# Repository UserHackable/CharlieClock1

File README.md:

## SevenSegmentArrays 

### Board dimensions

* (310000, 200000) original units
* (3.1000, 2.0000) inches
* (78.7400, 50.8000) mm

| Front | Back |
| --- | --- |
|  |  |

## SevenSegmentBreakout 

### Board dimensions

* (365000, 130000) original units
* (3.6500, 1.3000) inches
* (92.7100, 33.0200) mm

| Front | Back |
| --- | --- |
|  |  |

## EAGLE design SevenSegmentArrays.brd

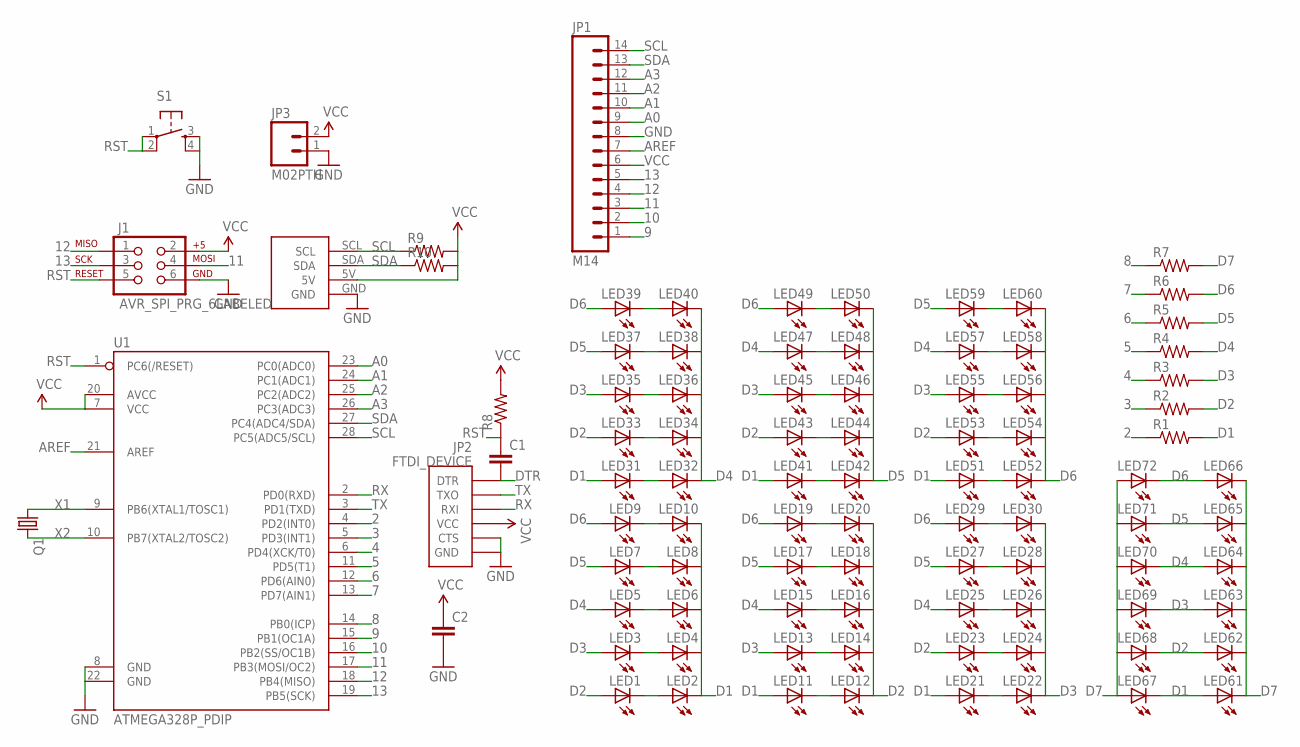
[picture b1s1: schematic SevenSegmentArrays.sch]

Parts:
C1, C2: CAPPTH; CAP-PTH-SMALL
J1: AVR_SPI_PRG_6LABELED; 2X3-NS
JP1: M14; 1X14
JP2: FTDI_DEVICE; FTDI_DEVICE_SIDE
JP3: M02PTH; 1X02
LED1, LED2, LED3, LED4, LED5, LED6, LED7, LED8, LED9, LED10, LED11, LED12, LED13, LED14, LED15, LED16, LED17, LED18, LED19, LED20, LED21, LED22, LED23, LED24, LED25, LED26, LED27, LED28, LED29, LED30, LED31, LED32, LED33, LED34, LED35, LED36, LED37, LED38, LED39, LED40, LED41, LED42, LED43, LED44, LED45, LED46, LED47, LED48, LED49, LED50, LED51, LED52, LED53, LED54, LED55, LED56: LEDRECT; RECTANGLE_LED
LED57, LED58, LED59, LED60, LED61, LED62, LED63, LED64, LED65, LED66, LED67, LED68, LED69, LED70, LED71, LED72: LED3MM
Q1: CRYSTALTC38H; TC38H
R1, R2, R3, R4, R5, R6, R7, R8, R9, R10: RESISTORAXIAL-0.3; AXIAL-0.3
S1: TAC_SWITCHPTH; TACTILE-PTH
U1: ATMEGA328P_PDIP; DIL28-3
U$1: I2C

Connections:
2: R1.P$1 (1), U1.4 (PD2(INT0))
3: R2.P$1 (1), U1.5 (PD3(INT1))
4: R3.P$1 (1), U1.6 (PD4(XCK/T0))
5: R4.P$1 (1), U1.11 (PD5(T1))
6: R5.P$1 (1), U1.12 (PD6(AIN0))
7: R6.P$1 (1), U1.13 (PD7(AIN1))
8: R7.P$1 (1), U1.14 (PB0(ICP))
9: JP1.1, U1.15 (PB1(OC1A))
10: JP1.2, U1.16 (PB2(SS/OC1B))
11: J1.4, JP1.3, U1.17 (PB3(MOSI/OC2))
12: J1.1, JP1.4, U1.18 (PB4(MISO))
13: J1.3, JP1.5, U1.19 (PB5(SCK))
A0: JP1.9, U1.23 (PC0(ADC0))
A1: JP1.10, U1.24 (PC1(ADC1))
A2: JP1.11, U1.25 (PC2(ADC2))
A3: JP1.12, U1.26 (PC3(ADC3))
AREF: JP1.7, U1.21 (AREF)
D1: LED2.C, LED4.C, LED6.C, LED8.C, LED10.C, LED11.A, LED21.A, LED31.A, LED41.A, LED51.A, LED61.A, LED67.K (C), R1.P$2 (2)
D2: LED1.A, LED12.C, LED14.C, LED16.C, LED18.C, LED20.C, LED23.A, LED33.A, LED43.A, LED53.A, LED62.A, LED68.K (C), R2.P$2 (2)
D3: LED3.A, LED13.A, LED22.C, LED24.C, LED26.C, LED28.C, LED30.C, LED35.A, LED45.A, LED55.A, LED63.A, LED69.K (C), R3.P$2 (2)
D4: LED5.A, LED15.A, LED25.A, LED32.C, LED34.C, LED36.C, LED38.C, LED40.C, LED47.A, LED57.A, LED64.A, LED70.K (C), R4.P$2 (2)
D5: LED7.A, LED17.A, LED27.A, LED37.A, LED42.C, LED44.C, LED46.C, LED48.C, LED50.C, LED59.A, LED65.A, LED71.K (C), R5.P$2 (2)
D6: LED9.A, LED19.A, LED29.A, LED39.A, LED49.A, LED52.C, LED54.C, LED56.C, LED58.K (C), LED60.K (C), LED66.A, LED72.K (C), R6.P$2 (2)
D7: LED61.K (C), LED62.K (C), LED63.K (C), LED64.K (C), LED65.K (C), LED66.K (C), LED67.A, LED68.A, LED69.A, LED70.A, LED71.A, LED72.A, R7.P$2 (2)
DTR: C1.2, JP2.P$1 (DTR)
GND: C2.2, J1.6, JP1.8, JP2.P$5 (CTS), JP2.P$6 (GND), JP3.1, S1.3, S1.4, U1.8 (GND), U1.22 (GND), U$1.GND
unnamed: LED1.C, LED2.A
unnamed: LED3.C, LED4.A
unnamed: LED5.C, LED6.A
unnamed: LED7.C, LED8.A
unnamed: LED9.C, LED10.A
unnamed: LED11.C, LED12.A
unnamed: LED13.C, LED14.A
unnamed: LED15.C, LED16.A
unnamed: LED17.C, LED18.A
unnamed: LED19.C, LED20.A
unnamed: LED21.C, LED22.A
unnamed: LED23.C, LED24.A
unnamed: LED25.C, LED26.A
unnamed: LED27.C, LED28.A
unnamed: LED29.C, LED30.A
unnamed: LED31.C, LED32.A
unnamed: LED33.C, LED34.A
unnamed: LED35.C, LED36.A
unnamed: LED37.C, LED38.A
unnamed: LED39.C, LED40.A
unnamed: LED41.C, LED42.A
unnamed: LED43.C, LED44.A
unnamed: LED45.C, LED46.A
unnamed: LED47.C, LED48.A
unnamed: LED49.C, LED50.A
unnamed: LED51.C, LED52.A
unnamed: LED53.C, LED54.A
unnamed: LED55.C, LED56.A
unnamed: LED57.K (C), LED58.A
unnamed: LED59.K (C), LED60.A
RST: C1.1, J1.5, R8.P$1 (1), S1.1, S1.2, U1.1 (PC6(/RESET))
RX: JP2.P$3 (RXI), U1.2 (PD0(RXD))
SCL: JP1.14, R9.P$1 (1), U1.28 (PC5(ADC5/SCL)), U$1.SCL
SDA: JP1.13, R10.P$1 (1), U1.27 (PC4(ADC4/SDA)), U$1.SDA
TX: JP2.P$2 (TXO), U1.3 (PD1(TXD))
VCC: C2.1, J1.2, JP1.6, JP2.P$4 (VCC), JP3.2, R8.P$2 (2), R9.P$2 (2), R10.P$2 (2), U1.7 (VCC), U1.20 (AVCC), U$1.5V
X1: Q1.1, U1.9 (PB6(XTAL1/TOSC1))
X2: Q1.2, U1.10 (PB7(XTAL2/TOSC2))

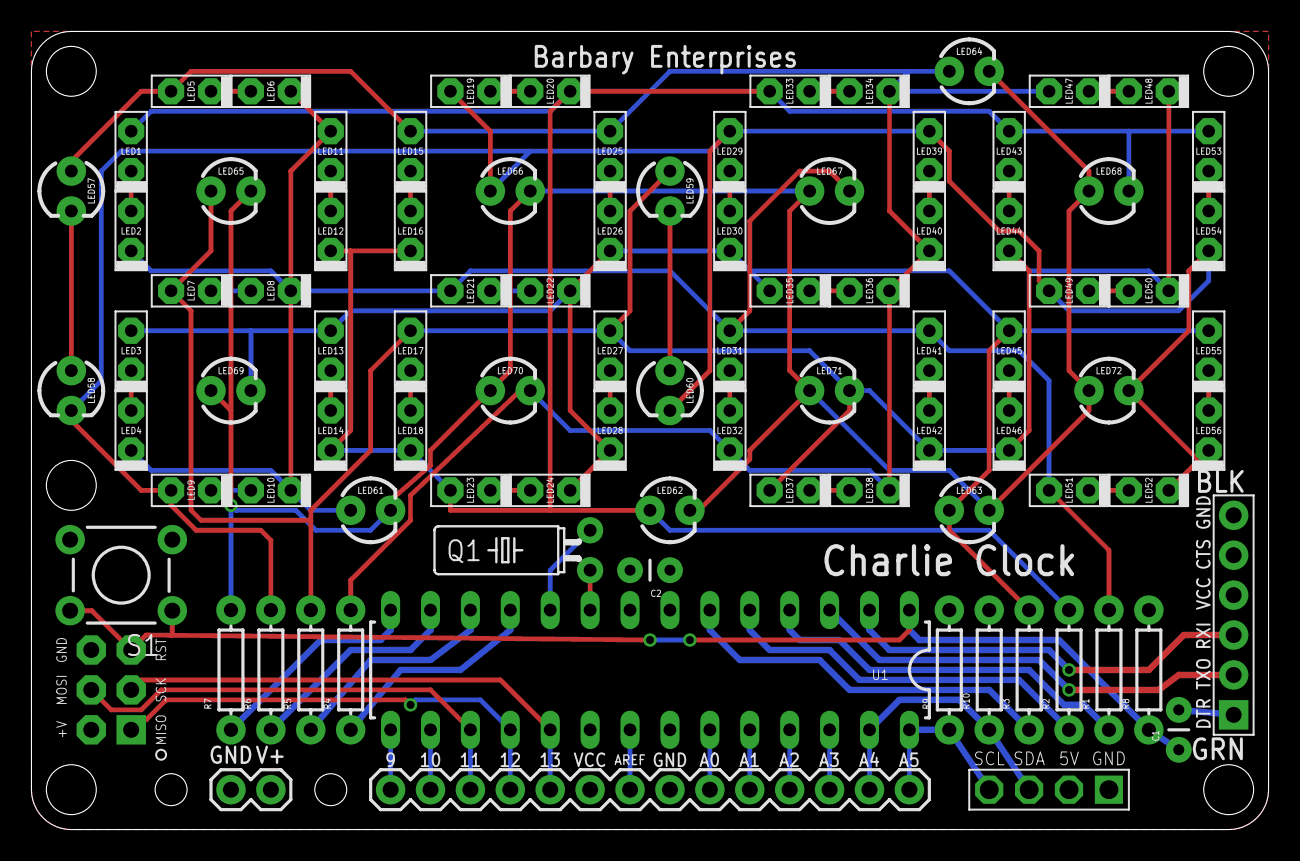
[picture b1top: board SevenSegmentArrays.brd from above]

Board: 2 copper layers, 78.7 x 50.8 mm, 92 parts (0 on the bottom side), 64 nets.

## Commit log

2016-04-08 from Makefile

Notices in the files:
parts and their libraries:
SparkFun-Connectors: Licensing: Creative Commons ShareAlike 4.0 International - https://creativecommons.org/licenses/by-sa/4.0
